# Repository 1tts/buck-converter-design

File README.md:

# Design & Schematics for 5V - 1.8V DC Synchronous Buck Converter

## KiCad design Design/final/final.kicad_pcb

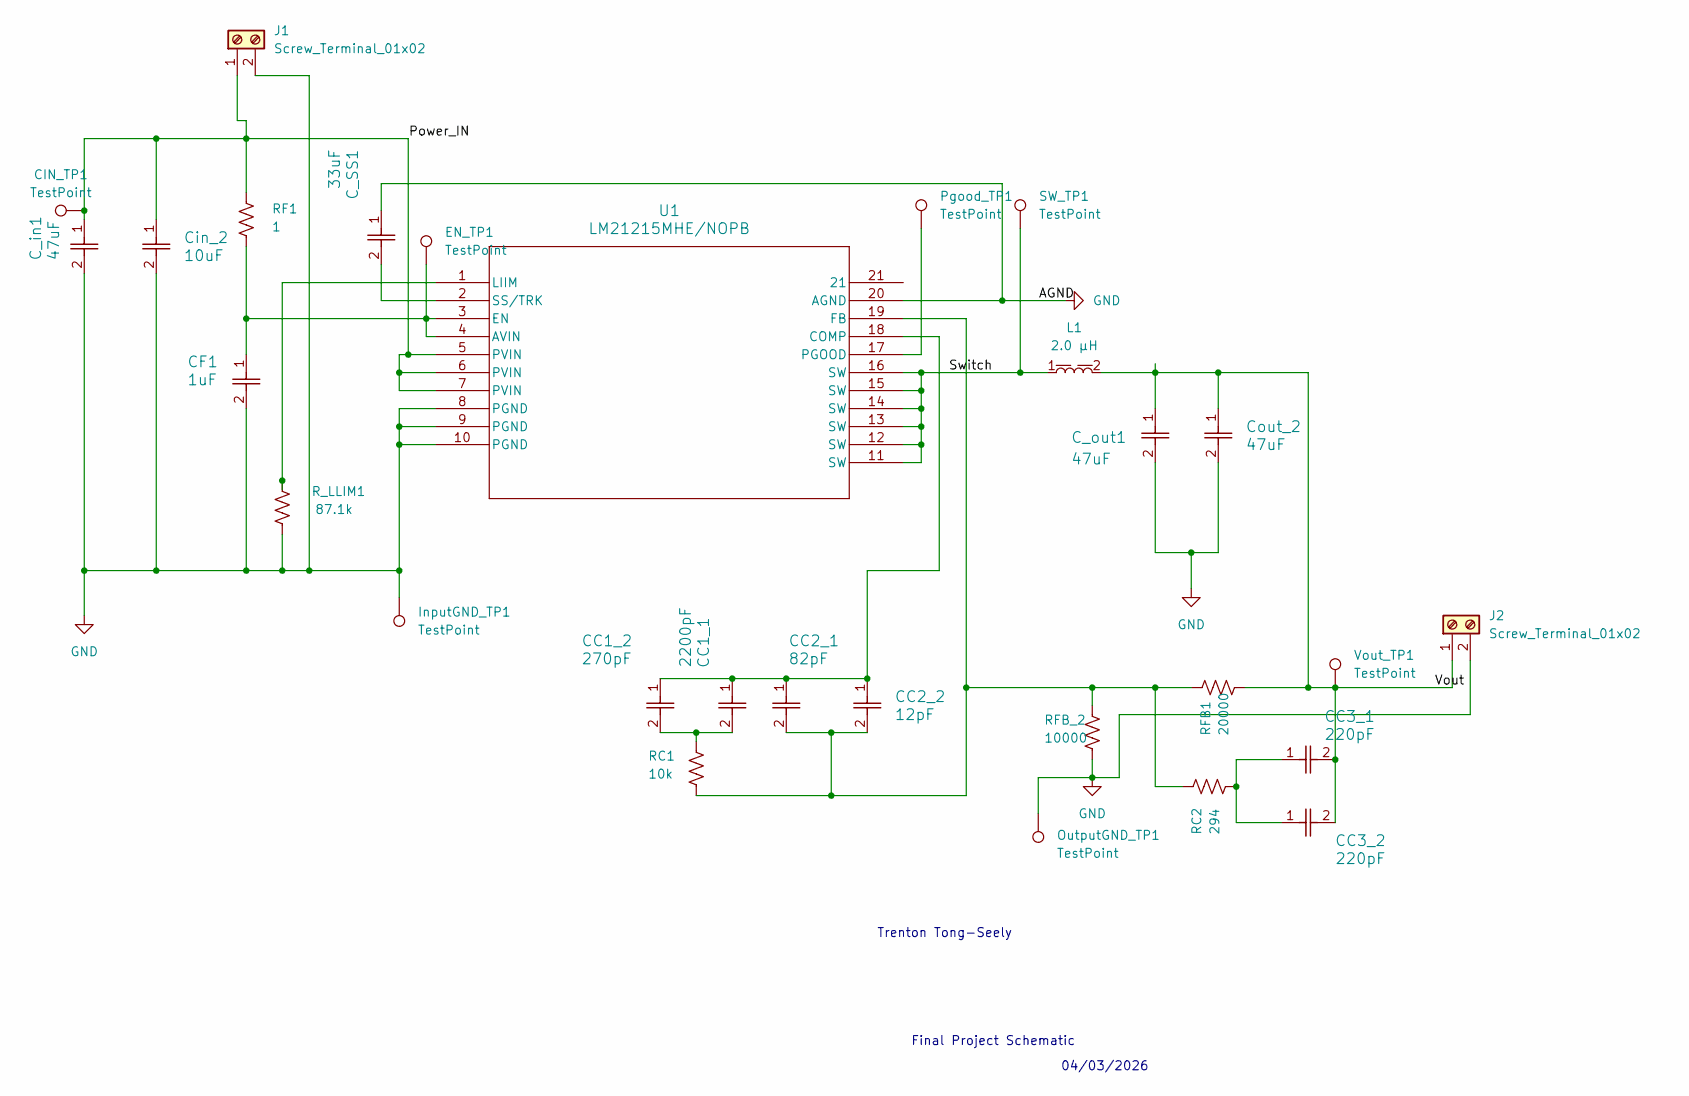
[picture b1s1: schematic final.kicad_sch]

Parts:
CC1_1: 2200pF; CAP_GRM_3p4x1p8x1_MUR
CC1_2: 270pF; CAP_1206J_AVX
CC2_1: 82pF; CAP_1206J_AVX
CC2_2: 12pF; CAP_1206J_AVX
CC3_1, CC3_2: 220pF; CAP_GRM_3p4x1p8x1_MUR
CF1: 1uF; CAP_1206J_AVX
CIN_TP1: TestPoint; TestPoint_THTPad_D2.0mm_Drill1.0mm
C_SS1: 33uF; CAP_GRM_3p4x1p8x1_MUR
C_in1: 47uF; CAP_GRM_3p4x1p8x1_MUR
C_out1: 47uF; CAP_GRM_3p4x1p8x1_MUR
Cin_2: 10uF; CAP_1206J_AVX
Cout_2: 47uF; CAP_GRM_3p4x1p8x1_MUR
EN_TP1: TestPoint; TestPoint_THTPad_D2.0mm_Drill1.0mm
InputGND_TP1: TestPoint; TestPoint_THTPad_D2.0mm_Drill1.0mm
J1, J2: Screw_Terminal_01x02; TerminalBlock_Phoenix_MKDS-1-2-3.81_1x02_P3.81mm_Horizontal
L1: 7030_7843100200; L_Wurth_WE-HCIA-7030; Part Number 7843100200
OutputGND_TP1: TestPoint; TestPoint_THTPad_D2.0mm_Drill1.0mm
Pgood_TP1: TestPoint; TestPoint_THTPad_D2.0mm_Drill1.0mm
RC1: 10k; R_1210_3225Metric
RC2: 294; R_1210_3225Metric
RF1: 1; R_1210_3225Metric
RFB1: 20000; R_1210_3225Metric
RFB_2: 10000; R_1210_3225Metric
R_LLIM1: 87.1k; R_1210_3225Metric
SW_TP1: TestPoint; TestPoint_THTPad_D2.0mm_Drill1.0mm
U1: LM21215MHE/NOPB; MYB20AA
Vout_TP1: TestPoint; TestPoint_THTPad_D2.0mm_Drill1.0mm

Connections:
/<NO NET>: L1.1, SW_TP1.1 (1_1), U1.11 (SW), U1.12 (SW), U1.13 (SW), U1.14 (SW), U1.15 (SW), U1.16 (SW)
/Power_IN: CIN_TP1.1 (1_1), C_in1.1, Cin_2.1, J1.1, RF1.1, U1.5 (PVIN), U1.6 (PVIN), U1.7 (PVIN)
/Vout: CC3_1.2, CC3_2.2, C_out1.1, Cout_2.1, J2.1, L1.2, RFB1.2, Vout_TP1.1 (1_1)
GND: CF1.2, C_SS1.1, C_in1.2, C_out1.2, Cin_2.2, Cout_2.2, InputGND_TP1.1 (1_1), J1.2, J2.2, OutputGND_TP1.1 (1_1), RFB_2.2, R_LLIM1.2, U1.8 (PGND), U1.9 (PGND), U1.10 (PGND), U1.20 (AGND), U1.EPAD
unnamed: CC1_1.2, CC1_2.2, RC1.1
unnamed: CC3_1.1, CC3_2.1, RC2.2
unnamed: CF1.1, EN_TP1.1 (1_1), RF1.2, U1.3 (EN), U1.4 (AVIN)
unnamed: CC1_1.1, CC1_2.1, CC2_1.1, CC2_2.1, U1.18 (COMP)
unnamed: CC2_1.2, CC2_2.2, RC1.2, RC2.1, RFB1.1, RFB_2.1, U1.19 (FB)
unnamed: R_LLIM1.1, U1.1 (LIIM)
unnamed: Pgood_TP1.1 (1_1), U1.17 (PGOOD)
unnamed: C_SS1.2, U1.2 (SS/TRK)

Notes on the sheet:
Final Project Schematic
Trenton Tong-Seely
04/03/2026

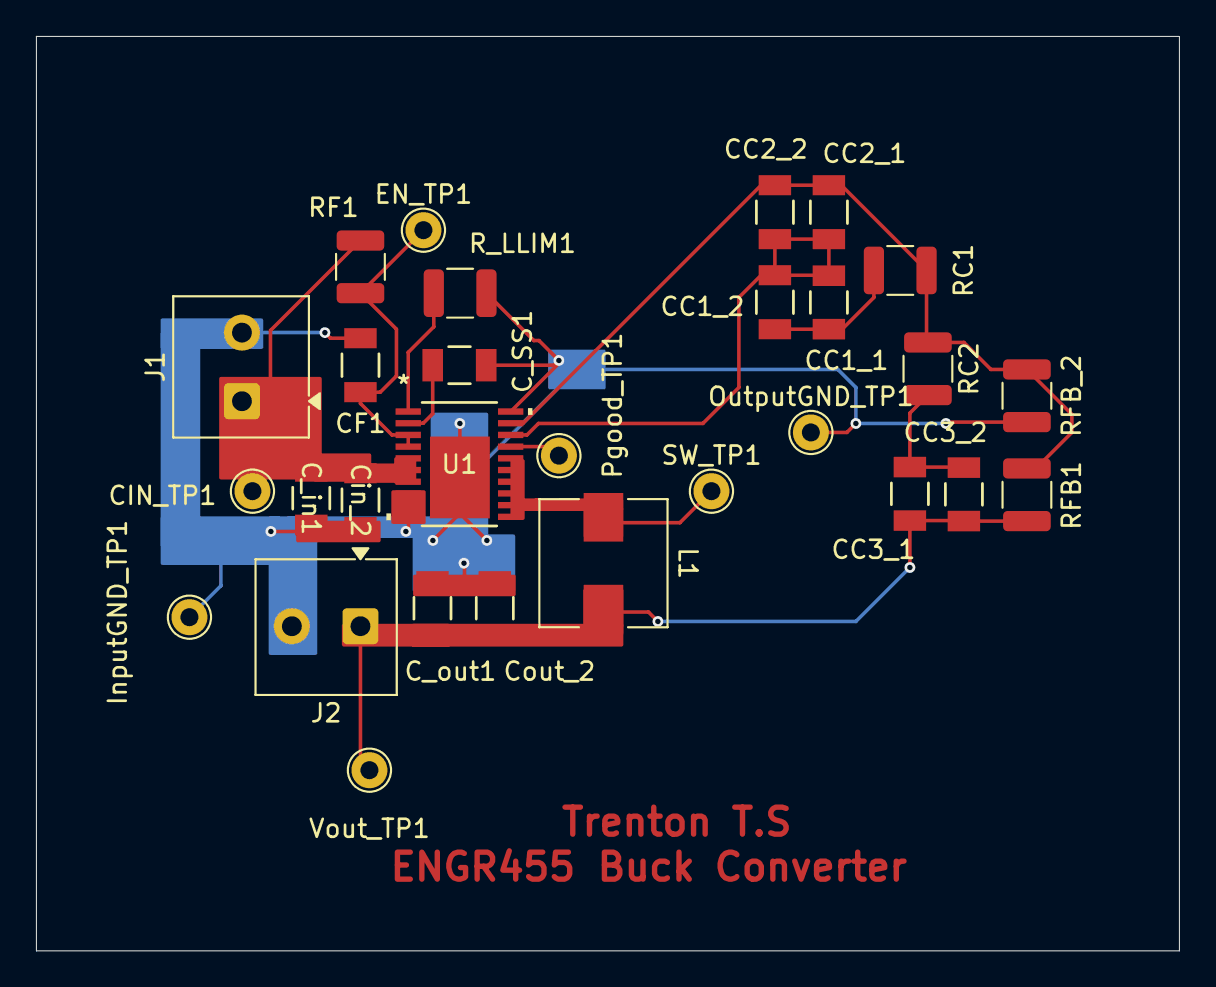
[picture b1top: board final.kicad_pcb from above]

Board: 2 copper layers, 63.5 x 50.8 mm, 29 parts (0 on the bottom side), 12 nets.
